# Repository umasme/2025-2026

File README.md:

# 🚀 NASA Lunabotics 2026 — University of Miami ASME

Robust, ROS 2–based software stack and supporting assets for our lunar excavation rover.  
This repository houses **software, hardware, simulation, datasets, and documentation** to support the NASA Lunabotics 2026 competition.  

---
## To Build
1. Download Docker
2. Open VS Code and switch to WS directory
3. Install the dev containers extension
4. Control + Shift + P to access command palette
5. Search for Dev Containers: Reopen in Container
6. Voila

## Sensors
1. D435i (TBD)
2. Oak D-lite (TBD)
3. Power sensor
4. Encoders
5. Linear encoders
6. Cameras

## Actuators
1. Four motors
2. Linear Actuators

## After Each Commit
Update DEVLOG.md with a summary of changes. Commits shall be made to the develop branch after main branch docker is working.

## 📖 Project Overview

Our rover integrates:

- **Perception** — stereo depth, object detection, terrain mapping  
- **Localization & Navigation** — SLAM, sensor fusion, path planning  
- **Autonomy** — state machines / behavior trees for excavation & hauling  
- **Control & Teleop** — motor drivers, teleop interfaces, web dashboard  
- **Simulation** — Ignition Gazebo worlds, scenarios, and URDF models  
- **Documentation** — aligned with NASA Systems Engineering (SRR, PDR, CDR, ConOps)  

---

## 📂 Repository Layout

```text
lunabotics-2025/
├─ README.md                     # Project overview (this file)
├─ LICENSE
├─ .github/workflows/            # CI/CD pipelines
├─ .devcontainer/                # VS Code Dev Containers
├─ docker/                       # Development & runtime Dockerfiles
├─ docs/                         # Documentation
│  ├─ index.md
│  ├─ ConOps/                    # SRR/PDR/CDR deliverables
│  ├─ Architectures/             # Block/state diagrams
│  ├─ MissionRules/              # Ops rules, FMEA links
│  ├─ Tutorials/                 # Step-by-step guides
│  └─ Calibration/               # Sensor/actuator calibration
├─ hardware/                     # Mechanical + electrical
│  ├─ electrical/                # Schematics, PCB, BOM
│  ├─ mechanical/                # CAD models, drawings
│  └─ configs/                   # Wiring tables, pin maps
├─ datasets/                     # Large files (via Git LFS)
│  ├─ bags/                      # ROS bag recordings
│  ├─ maps/                      # Occupancy/elevation maps
│  └─ test_scenes/               # Images, point clouds
├─ sim/                          # Simulation assets
│  ├─ worlds/                    # Ignition/Gazebo worlds
│  ├─ models/                    # URDF meshes, STL/DAE
│  └─ scenarios/                 # Scenario configs
├─ examples/                     # Cross-package & full-system demos
│  ├─ sim_demo.launch.py
│  ├─ teleop_example.md
│  └─ rviz_configs/
├─ tools/                        # Utility scripts
│  ├─ log_tools/                 # Bag→CSV, plotting
│  ├─ calibration/               # Camera/IMU calibration
│  ├─ deploy/                    # Deployment helpers
│  └─ ci/                        # CI support scripts
└─ ros2_ws/                      # ROS 2 workspace
   ├─ src/
   │  ├─ lunabotics_bringup/     # System launch & params
   │  ├─ lunabotics_description/ # URDF/Xacro and meshes
   │  ├─ lunabotics_msgs/        # Custom messages & services
   │  ├─ lunabotics_hw/          # Hardware drivers
   │  ├─ lunabotics_perception/  # Cameras, detection
   │  ├─ lunabotics_mapping/     # SLAM & maps
   │  ├─ lunabotics_localization/# State estimation
   │  ├─ lunabotics_navigation/  # Planning & control
   │  ├─ lunabotics_control/     # Low-level control loops
   │  ├─ lunabotics_mission/     # Autonomy FSM/BT
   │  ├─ lunabotics_teleop/      # Joystick / keyboard teleop
   │  ├─ lunabotics_dashboard/   # Web UI & ROS bridge
   │  └─ lunabotics_sim/         # Simulation plugins & launches
   ├─ build/                     # (ignored) colcon build output
   ├─ install/                   # (ignored) colcon install
   └─ log/                       # (ignored) colcon logs

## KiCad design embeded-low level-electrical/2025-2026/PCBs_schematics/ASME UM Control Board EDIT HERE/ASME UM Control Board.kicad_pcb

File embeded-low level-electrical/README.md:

# 🚀 ASME Lunabotics 2026 University of Miami – Electrical Subsystem

Welcome to the official repository for the electrical subsystem of the University of Miami’s ASME Lunabotics team for the **2026 NASA Lunabotics Competition**.

---

This repository documents the design, implementation, and testing of the rover’s electrical system, emphasizing high reliability, efficiency, and simplicity.

# 2026 Design Goals

- Design an effective system with high reliability, minimal points of failure, and strategic redundancies while keeping it simple with minimal components and maximum efficiency.

- Focus on real-time data logging of current, voltage, power, temperature, and speed for post-analysis and future optimization.

- Reduce wiring complexity by using multiplexed communication protocols.

- Ensure reliable wired communication and power distribution to motors and other subsystems.
---
# 2026 Proposed Electrical Architecture

<p align="center">
  
  <p align="center">
  <b> High Voltage Electrical Architecture </b>
  </p>
</p>

  <p align="center">
  <b> Control Electrical Architecture </b>
  </p>

---
## High-Current Power Distribution Board
This high-current board distributes power to all outputs, including the four drivetrain motors, the excavation motor, the deposition motor, and two linear actuators.

<p align="center">
  <b> High-Current Power Distribution Board PCB </b>
</p>

For more details refer to this link: [to be added]

---
## Low-Level Control Board based on Teensy 4.1

<p align="center">
  <b> Low-Level Control Board based on Teensy 4.1 PCB </b>
</p>

For more details refer to this link: [To be added]

---
##  🎯2026 Season Plan 
We finalized the season plan for 2026 for the electrical subsystem with detailed performance analysis for each part we used in the electrical system and proposed improvement.

**[Click here to access the 2025 season plan](https://www.overleaf.com/read/gmnmmjygcdmp#dd8f39)**

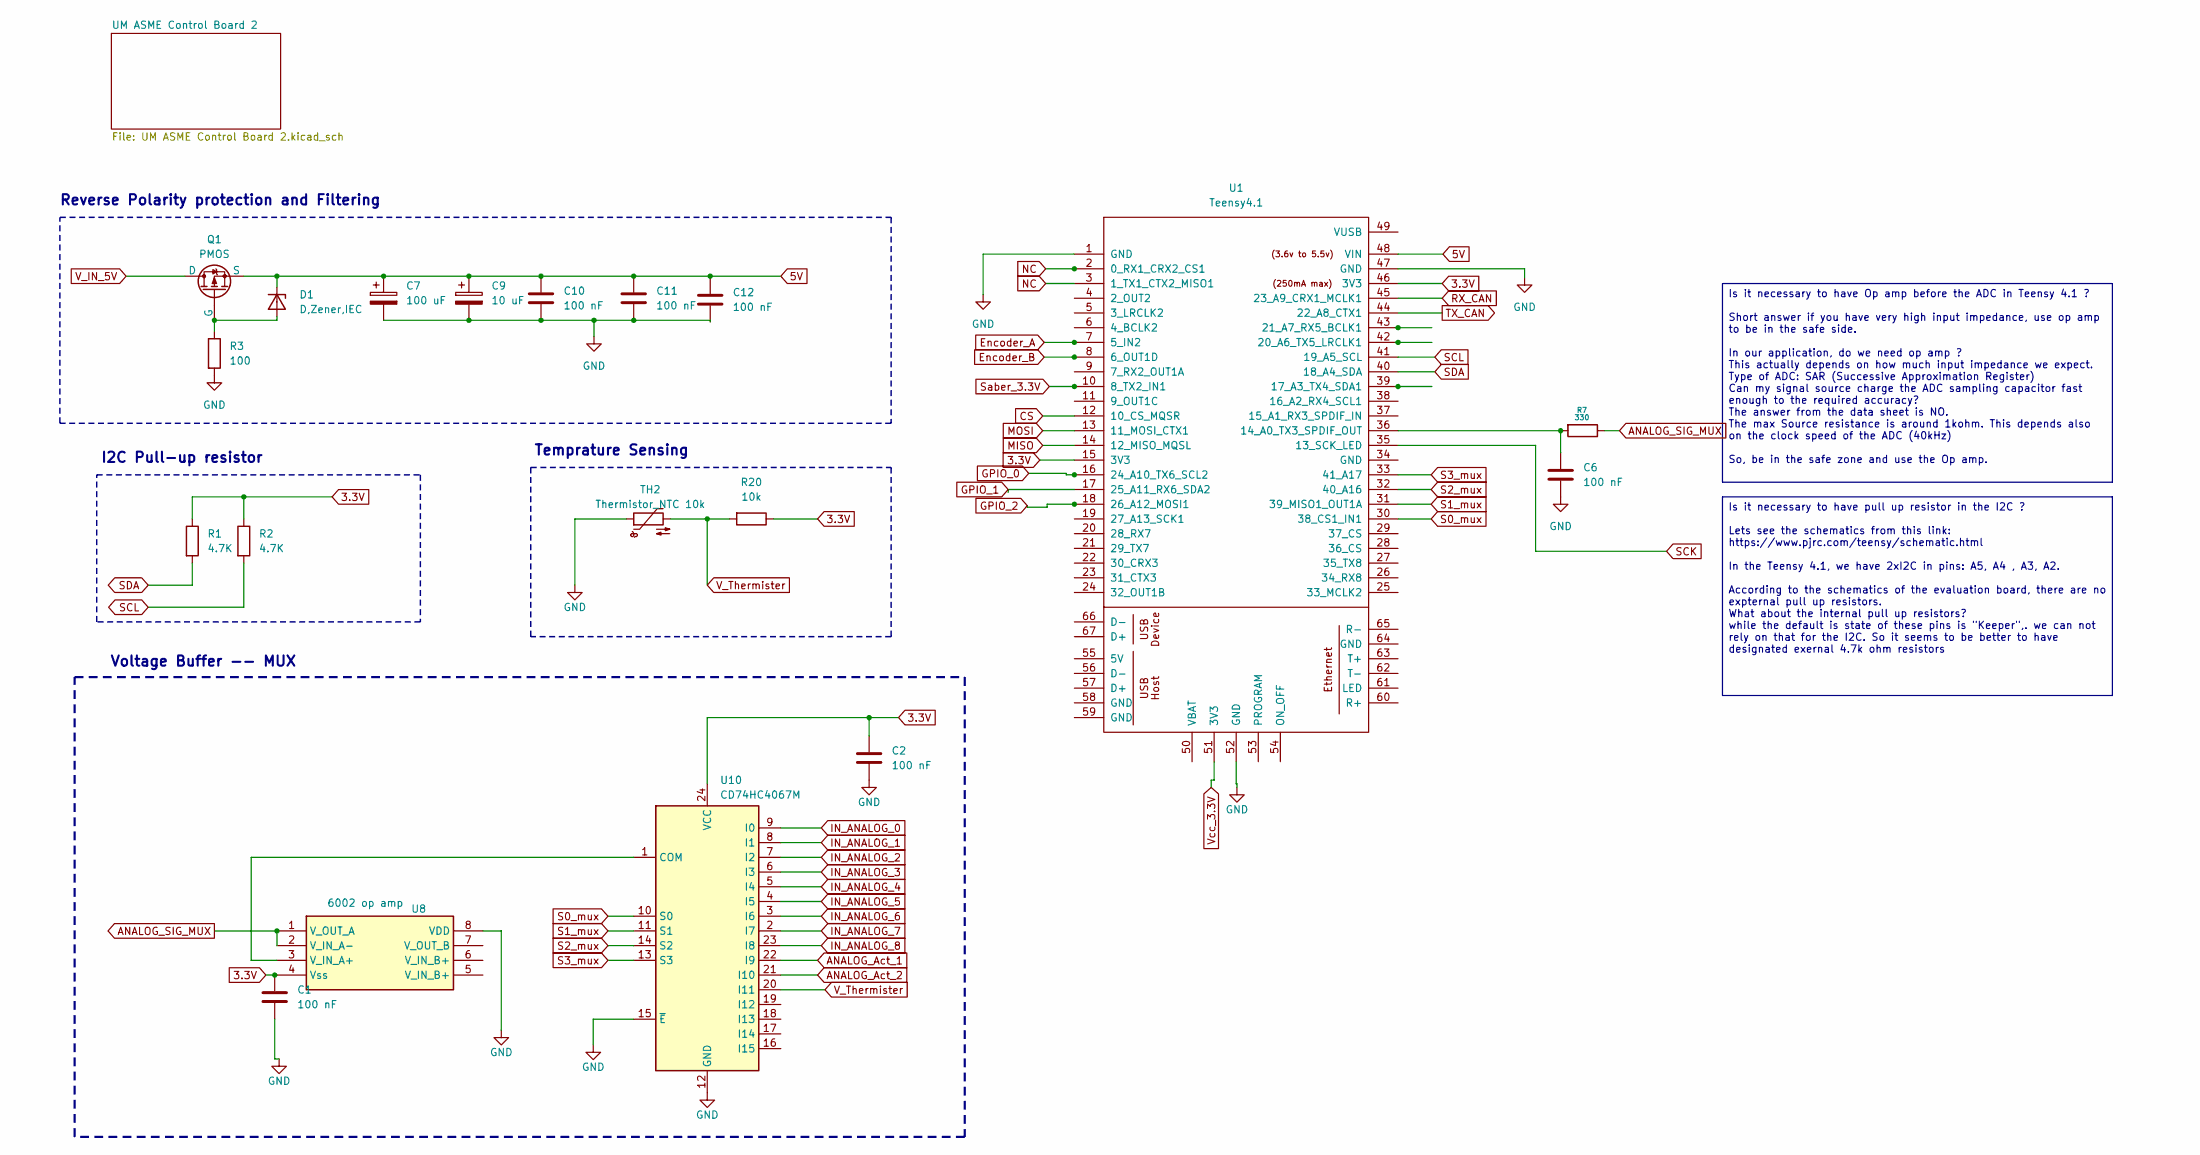
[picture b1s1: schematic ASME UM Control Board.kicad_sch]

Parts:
C1, C2, C6, C10, C11, C12: 100 nF; C_1206_3216Metric_Pad1.33x1.80mm_HandSolder
C7: 100 uF; CP_Radial_D8.0mm_P2.50mm
C9: 10 uF; C_1206_3216Metric_Pad1.33x1.80mm_HandSolder
D1: D,Zener,IEC; D_DO-35_SOD27_P7.62mm_Horizontal
Q1: PMOS; TO-220-3_Vertical
R1, R2: 4.7K; R_1206_3216Metric_Pad1.30x1.75mm_HandSolder
R3: 100; R_1206_3216Metric_Pad1.30x1.75mm_HandSolder
R7: 330; R_1206_3216Metric_Pad1.30x1.75mm_HandSolder
R20: 10k; R_1206_3216Metric_Pad1.30x1.75mm_HandSolder
TH2: Thermistor_NTC 10k; 1210
U1: Teensy4.1; Teensy41
U8: 6002 op amp; DIP-8_W7.62mm_LongPads
U10: CD74HC4067M; SOIC-24W_7.5x15.4mm_P1.27mm

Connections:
3.3V: C1.1, C2.1, R1.1, R2.1, R20.1, U1.15 (3V3), U1.46 (3V3), U8.4 (Vss), U10.24 (VCC); also elsewhere on the board
5V: C7.1, C9.1, C10.1, C11.1, C12.1, D1.1 (K-), Q1.3 (S), U1.48 (VIN); also elsewhere on the board
ANALOG_Act_1: U10.22 (I9); also elsewhere on the board
ANALOG_Act_2: U10.21 (I10); also elsewhere on the board
ANALOG_SIG_MUX: R7.1, U8.1 (V_OUT_A), U8.2 (V_IN_A-)
CS: U1.12 (10_CS_MQSR)
Encoder_A: U1.7 (5_IN2); also elsewhere on the board
Encoder_B: U1.8 (6_OUT1D); also elsewhere on the board
GND: C1.2, C2.2, C6.2, C7.2, C9.2, C10.2, C11.2, C12.2, R3.2, TH2.1, U1.1 (GND), U1.47 (GND), U1.52 (GND), U8.8 (VDD), U10.12 (GND), U10.15 (~E); also elsewhere on the board
GPIO_0: U1.16 (24_A10_TX6_SCL2); also elsewhere on the board
GPIO_1: U1.17 (25_A11_RX6_SDA2); also elsewhere on the board
GPIO_2: U1.18 (26_A12_MOSI1); also elsewhere on the board
IN_ANALOG_0: U10.9 (I0); also elsewhere on the board
IN_ANALOG_1: U10.8 (I1); also elsewhere on the board
IN_ANALOG_2: U10.7 (I2); also elsewhere on the board
IN_ANALOG_3: U10.6 (I3); also elsewhere on the board
IN_ANALOG_4: U10.5 (I4); also elsewhere on the board
IN_ANALOG_5: U10.4 (I5); also elsewhere on the board
IN_ANALOG_6: U10.3 (I6); also elsewhere on the board
IN_ANALOG_7: U10.2 (I7); also elsewhere on the board
IN_ANALOG_8: U10.23 (I8); also elsewhere on the board
MISO: U1.14 (12_MISO_MQSL)
MOSI: U1.13 (11_MOSI_CTX1)
NC: U1.2 (0_RX1_CRX2_CS1), U1.3 (1_TX1_CTX2_MISO1)
unnamed: D1.2 (A+), Q1.2 (G), R3.1
unnamed: C6.1, R7.2, U1.36 (14_A0_TX3_SPDIF_OUT)
unnamed: U8.3 (V_IN_A+), U10.1 (COM)
RX_CAN: U1.45 (23_A9_CRX1_MCLK1); also elsewhere on the board
S0_mux: U1.30 (38_CS1_IN1), U10.10 (S0)
S1_mux: U1.31 (39_MISO1_OUT1A), U10.11 (S1)
S2_mux: U1.32 (40_A16), U10.14 (S2)
S3_mux: U1.33 (41_A17), U10.13 (S3)
SCK: U1.35 (13_SCK_LED)
SCL: R2.2, U1.41 (19_A5_SCL); also elsewhere on the board
SDA: R1.2, U1.40 (18_A4_SDA); also elsewhere on the board
Saber_3.3V: U1.10 (8_TX2_IN1); also elsewhere on the board
TX_CAN: U1.44 (22_A8_CTX1); also elsewhere on the board
V_IN_5V: Q1.1 (D); also elsewhere on the board
V_Thermister: R20.2, TH2.2, U10.20 (I11)

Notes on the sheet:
Voltage Buffer -- MUX
Temprature Sensing
Reverse Polarity protection and Filtering
I2C Pull-up resistor
Is it necessary to have Op amp before the ADC in Teensy 4.1 ? Short answer if you have very high input impedance, use op amp to be in the safe side. In our application, do we need op amp ? This actually depends on how much input impedance we expect. Type of ADC: SAR (Successive Approximation Regist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
Is it necessary to have pull up resistor in the I2C ? Lets see the schematics from this link: https://www.pjrc.com/teensy/schematic.html In the Teensy 4.1, we have 2xI2C in pins: A5, A4 , A3, A2. According to the schematics of the evaluation board, there are no expternal pull up resistors. What abo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

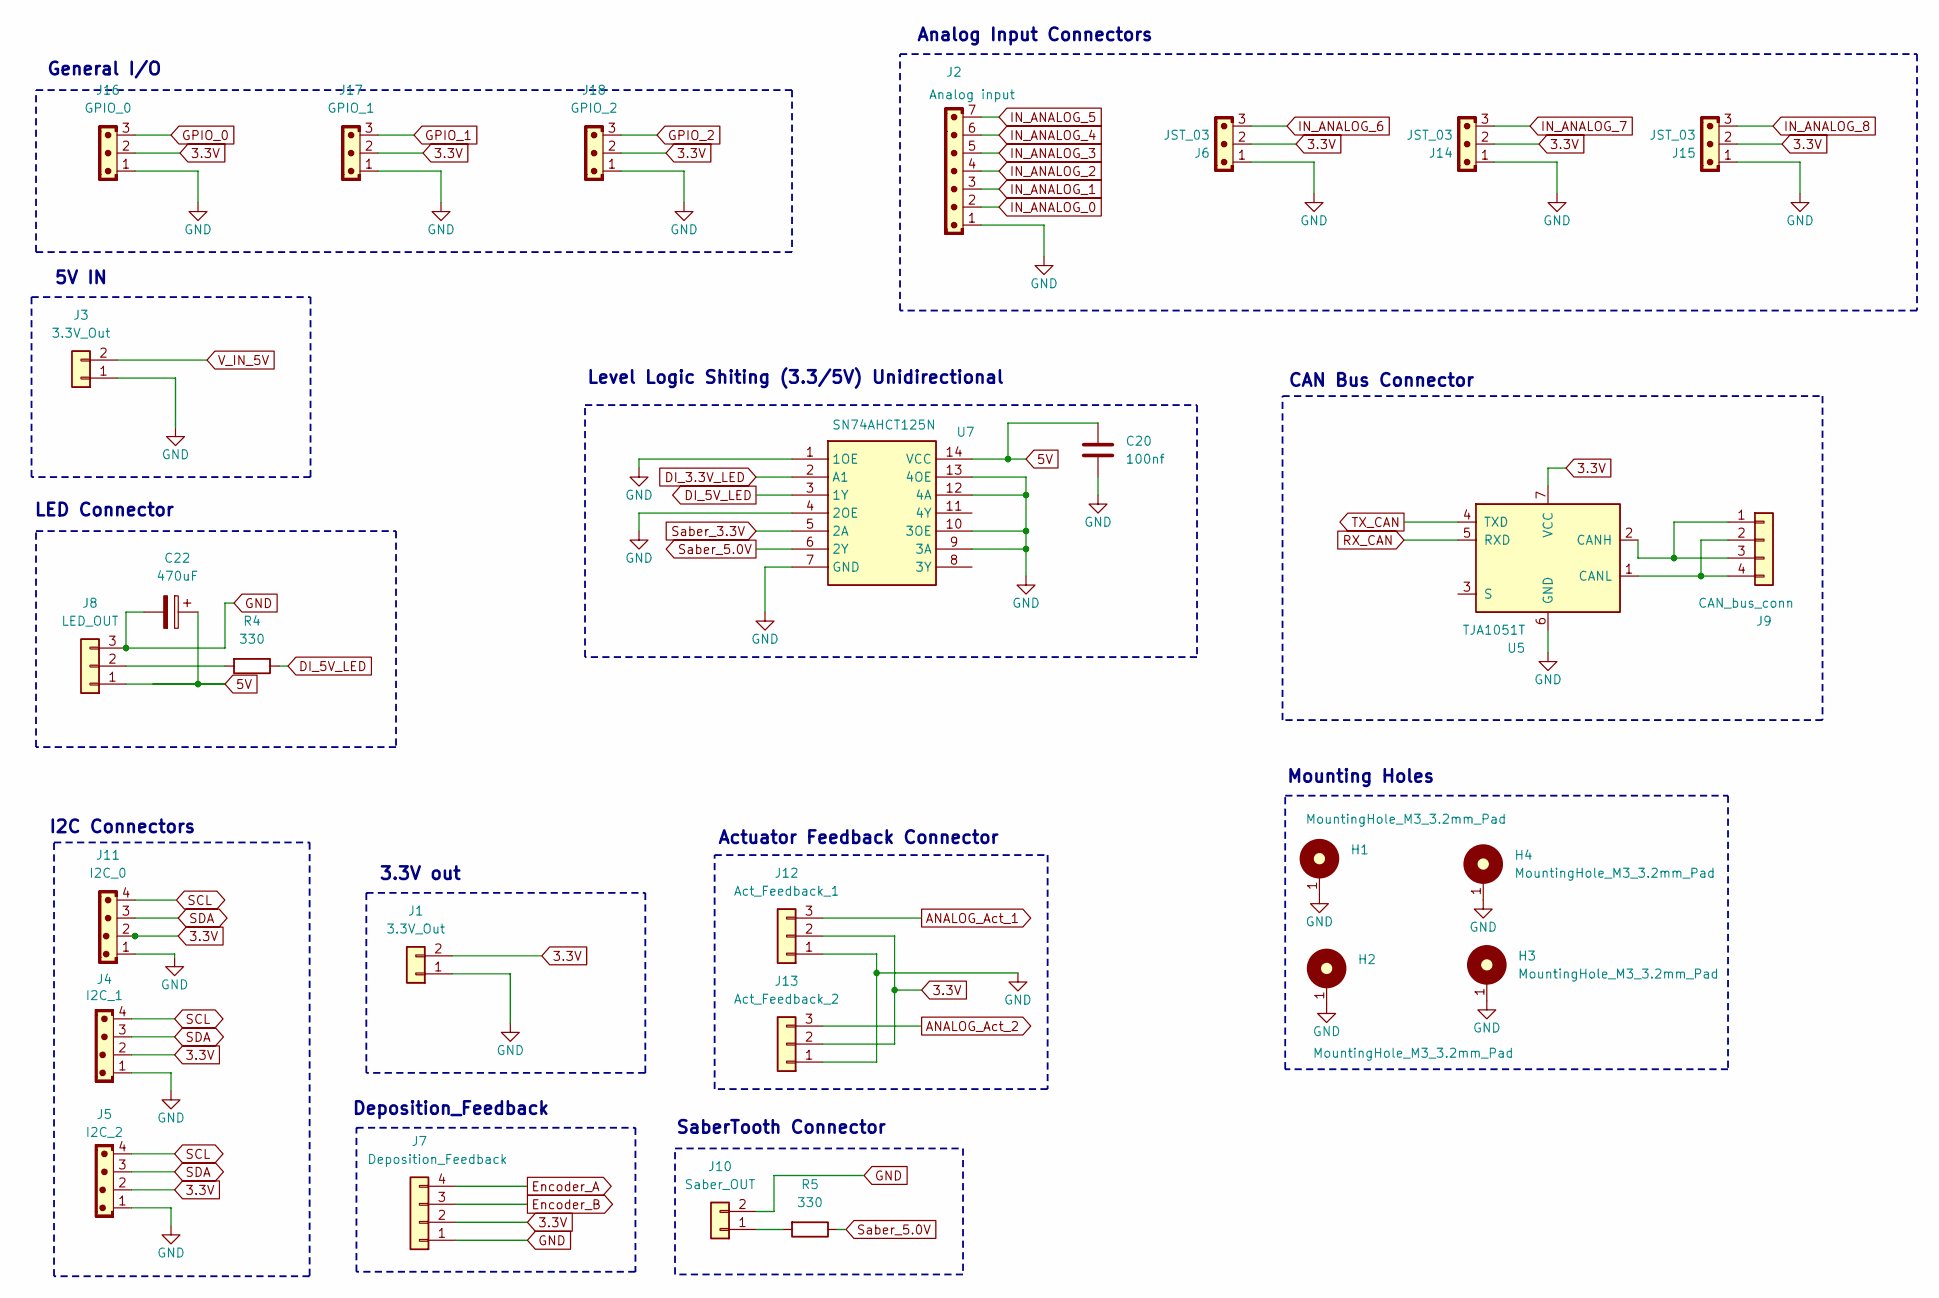
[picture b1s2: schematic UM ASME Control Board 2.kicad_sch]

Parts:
C20: 100nf; C_1206_3216Metric_Pad1.33x1.80mm_HandSolder
C22: 470uF; CP_Radial_D10.0mm_P3.80mm
H1, H2, H3, H4: MountingHole_M3_3.2mm_Pad; MountingHole_3.2mm_Pad
J1: 3.3V_Out; JST_PH_B2B-PH-K_1x02_P2.00mm_Vertical
J2: Analog input; JST_PH_B7B-PH-K_1x07_P2.00mm_Vertical
J3: 3.3V_Out; AMASS_XT30UPB-M_1x02_P5.0mm_Vertical
J4: I2C_1; JST_PH_B4B-PH-K_1x04_P2.00mm_Vertical
J5: I2C_2; JST_PH_B4B-PH-K_1x04_P2.00mm_Vertical
J6, J14, J15: JST_03; JST_PH_B3B-PH-K_1x03_P2.00mm_Vertical
J7: Deposition_Feedback; JST_PH_B4B-PH-K_1x04_P2.00mm_Vertical
J8: LED_OUT; JST_EH_B3B-EH-A_1x03_P2.50mm_Vertical
J9: CAN_bus_conn; JST_PH_B4B-PH-K_1x04_P2.00mm_Vertical
J10: Saber_OUT; JST_PH_B2B-PH-K_1x02_P2.00mm_Vertical
J11: I2C_0; JST_PH_B4B-PH-K_1x04_P2.00mm_Vertical
J12: Act_Feedback_1; JST_PH_B3B-PH-K_1x03_P2.00mm_Vertical
J13: Act_Feedback_2; JST_PH_B3B-PH-K_1x03_P2.00mm_Vertical
J16: GPIO_0; JST_PH_B3B-PH-K_1x03_P2.00mm_Vertical
J17: GPIO_1; JST_PH_B3B-PH-K_1x03_P2.00mm_Vertical
J18: GPIO_2; JST_PH_B3B-PH-K_1x03_P2.00mm_Vertical
R4, R5: 330; R_1206_3216Metric_Pad1.30x1.75mm_HandSolder
U5: TJA1051T; PinHeader_1x07_P2.54mm_Vertical
U7: SN74AHCT125N; DIP-14_W7.62mm_LongPads

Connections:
3.3V: J1.2, J4.2, J5.2, J6.2, J7.2, J11.2, J12.2, J13.2, J14.2, J15.2, J16.2, J17.2, J18.2, U5.7 (VCC); also elsewhere on the board
5V: C20.2, C22.1, J8.1, U7.14 (VCC); also elsewhere on the board
ANALOG_Act_1: J12.3; also elsewhere on the board
ANALOG_Act_2: J13.3; also elsewhere on the board
DI_3.3V_LED: U7.2 (A1)
DI_5V_LED: R4.1, U7.3 (1Y)
Encoder_A: J7.4; also elsewhere on the board
Encoder_B: J7.3; also elsewhere on the board
GND: C20.1, C22.2, H1.1, H2.1, H3.1, H4.1, J1.1, J2.1, J3.1, J4.1, J5.1, J6.1, J7.1, J8.3, J10.2, J11.1, J12.1, J13.1, J14.1, J15.1, J16.1, J17.1, J18.1, U5.6 (GND), U7.1 (1OE), U7.4 (2OE), U7.7 (GND), U7.9 (3A), U7.10 (3OE), U7.12 (4A), U7.13 (4OE); also elsewhere on the board
GPIO_0: J16.3; also elsewhere on the board
GPIO_1: J17.3; also elsewhere on the board
GPIO_2: J18.3; also elsewhere on the board
IN_ANALOG_0: J2.2; also elsewhere on the board
IN_ANALOG_1: J2.3; also elsewhere on the board
IN_ANALOG_2: J2.4; also elsewhere on the board
IN_ANALOG_3: J2.5; also elsewhere on the board
IN_ANALOG_4: J2.6; also elsewhere on the board
IN_ANALOG_5: J2.7; also elsewhere on the board
IN_ANALOG_6: J6.3; also elsewhere on the board
IN_ANALOG_7: J14.3; also elsewhere on the board
IN_ANALOG_8: J15.3; also elsewhere on the board
unnamed: J8.2, R4.2
unnamed: J9.1, J9.3, U5.2 (CANH)
unnamed: J9.2, J9.4, U5.1 (CANL)
unnamed: J10.1, R5.2
RX_CAN: U5.5 (RXD); also elsewhere on the board
SCL: J4.4, J5.4, J11.4; also elsewhere on the board
SDA: J4.3, J5.3, J11.3; also elsewhere on the board
Saber_3.3V: U7.5 (2A); also elsewhere on the board
Saber_5.0V: R5.1, U7.6 (2Y)
TX_CAN: U5.4 (TXD); also elsewhere on the board
V_IN_5V: J3.2; also elsewhere on the board

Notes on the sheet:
3.3V out
I2C Connectors
Deposition_Feedback
Level Logic Shiting (3.3/5V) Unidirectional
Mounting Holes
LED Connector
General I/O
5V IN
Actuator Feedback Connector
CAN Bus Connector
Analog Input Connectors
SaberTooth Connector

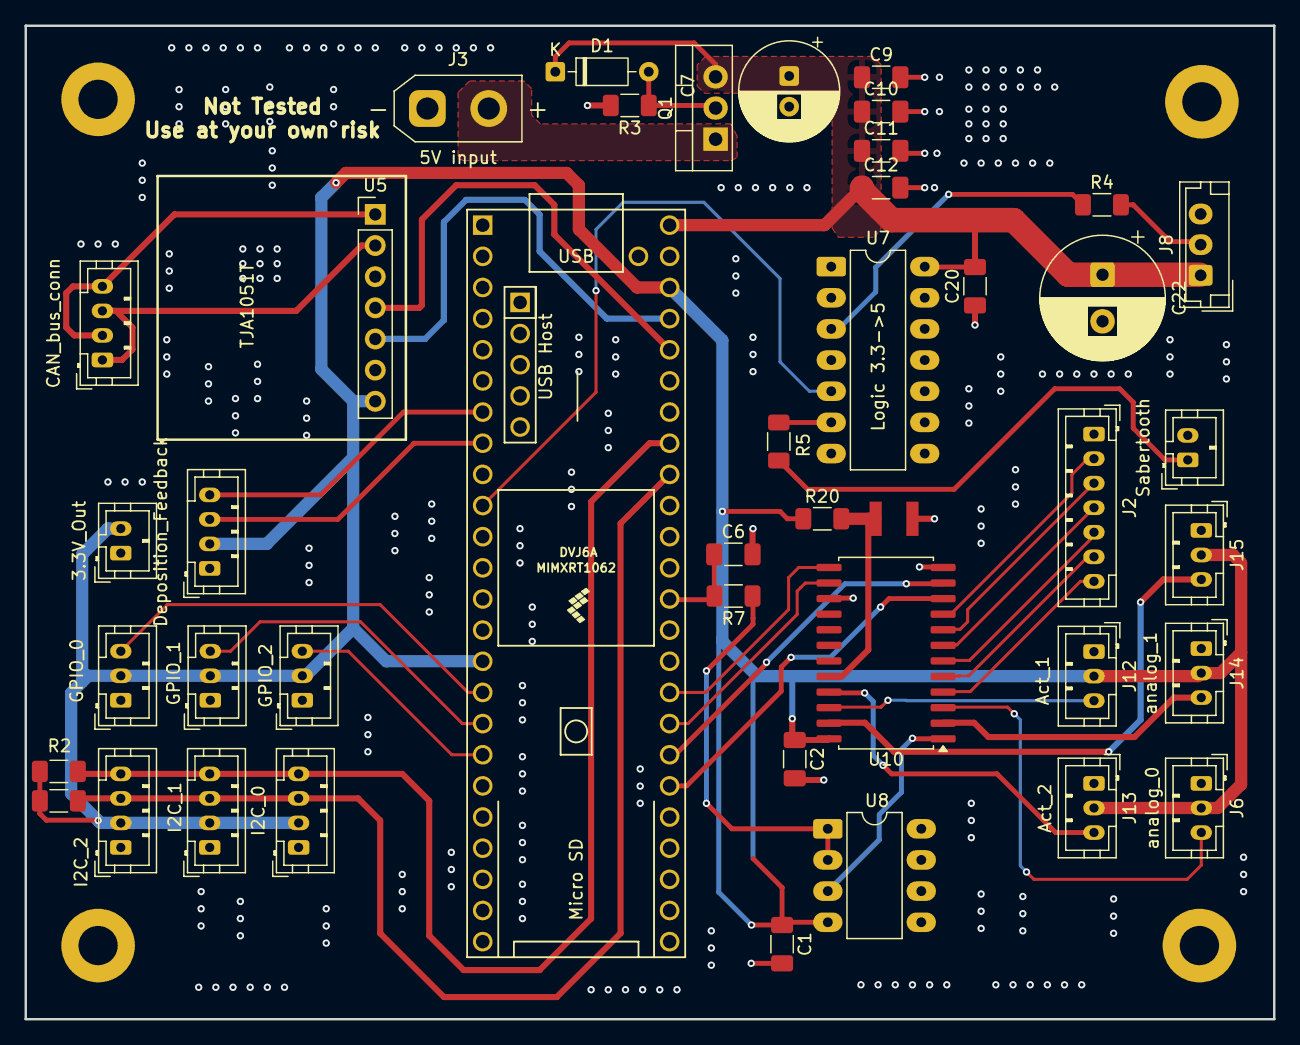
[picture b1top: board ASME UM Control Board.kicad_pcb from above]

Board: 4 copper layers, 101.8 x 81.0 mm, 47 parts (0 on the bottom side), 41 nets.

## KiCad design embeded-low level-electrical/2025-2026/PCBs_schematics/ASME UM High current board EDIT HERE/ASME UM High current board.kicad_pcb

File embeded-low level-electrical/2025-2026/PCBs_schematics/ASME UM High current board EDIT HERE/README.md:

# High-Current Power Distribution Board (PDB)

## Overview
The High-Current Power Distribution Board (PDB) is designed to safely and efficiently distribute electrical power to all high-power subsystems of the rover. It serves as the central power hub, handling high transient currents while providing protection, diagnostics, and future expandability.

## Supported Loads
This board distributes power to the following subsystems:

* **4×** Drivetrain motors (BLDC)
* **1×** Excavation motor (BLDC)
* **1×** Deposition motor (DC)
* **2×** Linear actuators 

> **Note:** The Jetson Nano is powered through an external power supply with a dedicated DC-DC converter and is **not** powered directly from this board.

## Electrical Capabilities
* **Peak Current:** Supports up to **40 A** peak current during startup and transient conditions.
* **Output Configuration:**
  * Minimum of **7** high-current outputs.
  * **1** dedicated output for a DC-DC converter.

## Board Features
* **Protection:** Reverse-polarity protection on the main power input and individual fuses for each output bus. (To be added)
* **Diagnostics:**
  * Power indication LED for board power status.
  * Individual LED indicators for each output to identify blown or faulted fuses.
* **Stability:** Decoupling capacitors for voltage stability and noise reduction.
* **Mechanical:** Defined mounting holes for secure mechanical integration.
* **Current Sensing:**
  * Initial revision includes main bus current sensor (or limited sensors).
  * PCB design preserves expandability for future per-output current sensing.
* ** Add-ons:**
  * Onboard DC-DC buck converter based on AP64502Q synchronous DC-DC buck converter (5V/5A). 
  * Linear 3.3 V regulator (not required for current system architecture).

## PCB Design Considerations
* **High-Current Optimization:** Adhered to IPC-2221 standards for power plane optimization to handle high-current loads and manage thermal dissipation.
* **Component Layout:** Strictly followed the recommended layout guidelines specified in the [AP64502Q DC-DC Converter Datasheet](https://www.diodes.com/datasheet/download/AP64502Q.pdf) to minimize noise and ensure stability.
* **Power Integrity Analysis:** Utilized Altium's Power Analyzer tool to simulate current density and eliminate bottlenecks.
<h3>Power Analyzer Results</h3>
<table width="100%">
  <tr>
    <th width="50%">Before Optimization</th>
    <th width="50%">After Optimization</th>
  </tr>
  <tr>
    <td align="center">
      
    </td>
    <td align="center">
      
    </td>
  </tr>
</table>## Design Objectives
* **Reliability:** Consistent operation under high-current and transient conditions.
* **Efficiency:** Low-resistance power paths to minimize voltage drop.
* **Usability:** Clear visual diagnostics for fast fault identification.

## Safety and Protection
* **Input:** Reverse-polarity protection.
* **Output:** Fuse protection per channel.
* **Visuals:** Fault detection via LED indicators.
* **Noise:** Electrical noise suppression using decoupling capacitors.

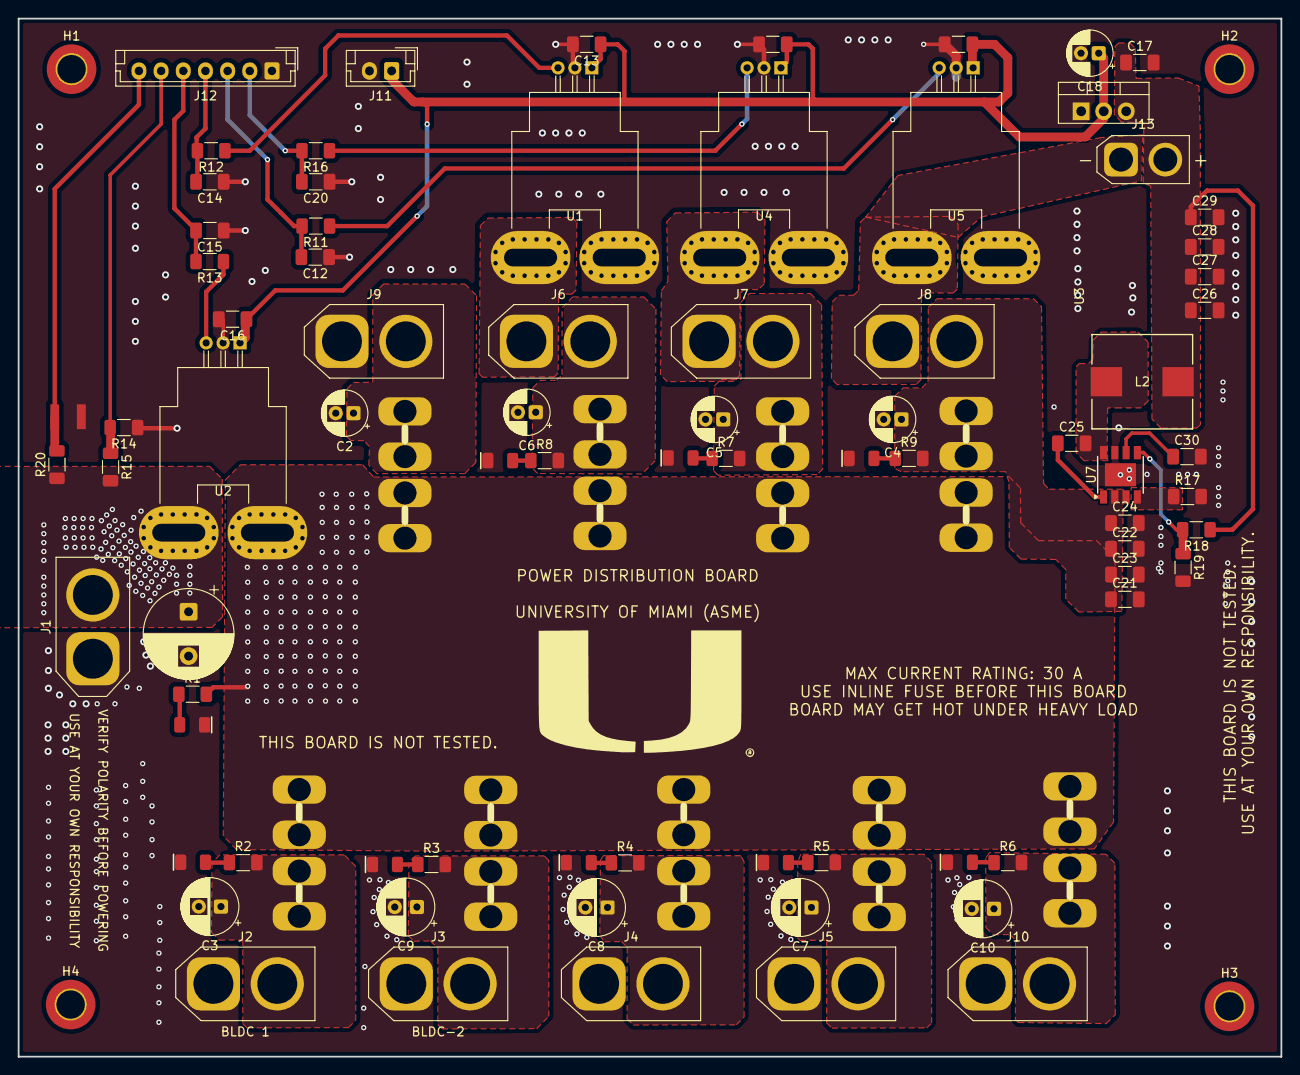
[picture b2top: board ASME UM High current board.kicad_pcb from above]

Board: 2 copper layers, 142.4 x 117.1 mm, 92 parts (0 on the bottom side), 41 nets.

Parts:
C1: 1000uF_16V; CP_Radial_D10.0mm_P5.00mm
C2, C4, C5, C6: 10uF_16V; CP_Radial_D5.0mm_P2.00mm
C3, C7, C8, C9, C10: 100uF_25V; CP_Radial_D6.3mm_P2.50mm
C11, C13, C16, C19: 100nF_Ceramic; C_1206_3216Metric_Pad1.33x1.80mm_HandSolder
C12, C14, C15, C20: 100nF; C_1206_3216Metric_Pad1.33x1.80mm_HandSolder
C17, C25, C26: 0.1uF; C_1206_3216Metric_Pad1.33x1.80mm_HandSolder
C18: 10uF; CP_Radial_D5.0mm_P2.00mm
C21: Open; C_1206_3216Metric_Pad1.33x1.80mm_HandSolder
C22, C23, C24: 10uF; C_1206_3216Metric_Pad1.33x1.80mm_HandSolder
C27, C28, C29: 47uF; C_1206_3216Metric_Pad1.33x1.80mm_HandSolder
C30: 10nF; C_1206_3216Metric_Pad1.33x1.80mm_HandSolder
D1: Red; LED_1206_3216Metric_Red
D2, D3, D4, D5, D6, D7, D8, D9: Green; LED_1206_3216Metric_Green
F1, F2, F3, F4, F5, F6, F7, F8, F9: Blade Fuse; Fuseholder_Automotive
H1, H2, H3, H4: MountingHole_M3; MountingHole_3.2mm_M3_DIN965_Pad_TopBottom
J1: From main battery; AMASS_XT60-M_1x02_P7.20mm_Vertical
J2: BLDC 1; AMASS_XT60-M_1x02_P7.20mm_Vertical
J3: BLDC-2; AMASS_XT60-M_1x02_P7.20mm_Vertical
J4: BLDC-3; AMASS_XT60-M_1x02_P7.20mm_Vertical
J5: BLDC-4; AMASS_XT60-M_1x02_P7.20mm_Vertical
J6: Actuators; AMASS_XT60-M_1x02_P7.20mm_Vertical
J7: Deposition; AMASS_XT60-M_1x02_P7.20mm_Vertical
J8: 5V DC-DC; AMASS_XT60-M_1x02_P7.20mm_Vertical
J9: Extra; AMASS_XT60-M_1x02_P7.20mm_Vertical
J10: BLDC-5; AMASS_XT60-M_1x02_P7.20mm_Vertical
J11: 3.3V_IN; JST_EH_B2B-EH-A_1x02_P2.50mm_Vertical
J12: JST_07; JST_EH_B7B-EH-A_1x07_P2.50mm_Vertical
J13: 5V_OUT; AMASS_XT30U-M_1x02_P5.0mm_Vertical
L2: 6.8uH; IND_PCC-M1040LP_PAN-M
R1: 1.5k; R_1206_3216Metric_Pad1.30x1.75mm_HandSolder
R2, R3, R4, R5, R6, R7, R8, R9: 1.2k; R_1206_3216Metric_Pad1.30x1.75mm_HandSolder
R11, R12, R13, R16: 4.7k; R_1206_3216Metric_Pad1.30x1.75mm_HandSolder
R14: 20k; R_1206_3216Metric_Pad1.30x1.75mm_HandSolder
R15: 100k; R_1206_3216Metric_Pad1.30x1.75mm_HandSolder
R17: 200k; R_1206_3216Metric_Pad1.30x1.75mm_HandSolder
R18: 52.3k; R_1206_3216Metric_Pad1.30x1.75mm_HandSolder
R19: 10k; R_1206_3216Metric_Pad1.30x1.75mm_HandSolder
R20: 47k; R_1206_3216Metric_Pad1.30x1.75mm_HandSolder
TH1: Thermistor_NTC 10k; 1210
U1, U4, U5: ACS758xCB-050B-PFF; Allegro_CB_PFF
U2: ACS772xCB-050B-PFF; Allegro_CB_PFF
U3: LD1117V33; TO-220-3_Vertical
U7: AP64502QSP‑13; Diodes_SO-8EP

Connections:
3.3V: C11.1, C13.1, C16.1, C18.1, C19.1, J11.1, U1.1 (VCC), U2.1 (VCC), U3.2 (VO), U4.1 (VCC), U5.1 (VCC)
5V_out: C17.1, C26.1, C27.1, C28.1, C29.1, J13.2, L2.2, R18.1, U3.3 (VI)
14V: C1.1, J1.2, R15.2, R20.1, U2.4 (IP+)
I_In_1: J6.1, U1.4 (IP+)
I_In_2: J7.1, U4.4 (IP+)
I_In_4: J8.1, J13.1, U5.4 (IP+)
I_Out_1: C1.2, C2.2, C3.2, C4.2, C5.2, C6.2, C7.2, C8.2, C9.2, C10.2, C11.2, C12.1, C13.2, C14.1, C15.1, C16.2, C17.2, C18.2, C19.2, C20.1, C21.2, C22.2, C23.2, C24.2, C26.2, C27.2, C28.2, C29.2, C30.2, D1.1 (K), D2.1 (K), D3.1 (K), D4.1 (K), D5.1 (K), D6.1 (K), D7.1 (K), D8.1 (K), D9.1 (K), J1.1, J2.1, J3.1, J4.1, J5.1, J9.1, J10.1, J11.2, J12.1, R14.1, R17.2, R19.2, TH1.1, U1.2 (GND), U1.5 (IP-), U2.2 (GND), U3.1 (GND), U4.2 (GND), U4.5 (IP-), U5.2 (GND), U5.5 (IP-), U7.7 (GND), U7.9 (GND)
I_Out_3: F1.2, F2.2, F3.2, F4.2, F5.2, F6.2, F7.2, F8.2, F9.2, R1.2, U2.5 (IP-)
unnamed: C2.1, F9.1, J9.2
unnamed: C3.1, F1.1, J2.2, R2.2
unnamed: C5.1, F7.1, J7.2, R7.2
unnamed: C6.1, F6.1, J6.2, R8.2
unnamed: C7.1, F4.1, J5.2, R5.2
unnamed: C8.1, F3.1, J4.2, R4.2
unnamed: C9.1, F2.1, J3.2, R3.2
unnamed: C10.1, F5.1, J10.2, R6.2
unnamed: D1.2 (A), R1.1
unnamed: D2.2 (A), R2.1
unnamed: D3.2 (A), R3.1
unnamed: D4.2 (A), R4.1
unnamed: D5.2 (A), R5.1
unnamed: D6.2 (A), R6.1
unnamed: D7.2 (A), R8.1
unnamed: D8.2 (A), R7.1
unnamed: D9.2 (A), R9.1
unnamed: R12.1, U1.3 (VIOUT)
unnamed: R13.1, U2.3 (VIOUT)
unnamed: R16.1, U4.3 (VIOUT)
unnamed: R11.1, U5.3 (VIOUT)
unnamed: C25.1, U7.1 (BST)
unnamed: R18.2, R19.1, U7.5 (FB)
unnamed: R17.1, U7.4 (RT/CLK)
unnamed: C30.1, U7.6 (SS)
unnamed: C25.2, L2.1, U7.8 (SW)
V_ANALOG_0: J12.6, R14.2, R15.1
V_ANALOG_1: C14.2, J12.4, R12.2
V_ANALOG_2: C20.2, J12.2, R16.2
V_ANALOG_3: C15.2, J12.5, R13.2
V_ANALOG_4: C12.2, J12.3, R11.2
V_ANALOG_5: J12.7, R20.2, TH1.2
V_in_DC-DC: C4.1, C21.1, C22.1, C23.1, C24.1, F8.1, J8.2, R9.2, U7.2 (Vin), U7.3 (EN)

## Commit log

2025-08-29 docs: Create Architecture.md
2025-08-29 docs: Add contributing guidelines to CONTRIBUTING.md
2025-08-29 feat: create ci.yaml
2025-08-29 docs: Create Makefile.md for command documentation
    Add a section for commonly used commands.
2025-08-29 docs: Add section for software architecture details
2025-08-29 Add initial README for Docker usage
2025-08-29 docs: Add README for electrical schematics
2025-08-29 docs: Add initial README for ROS project
2025-08-29 feat: Delete .github/workflows/ci.yaml
    This is good to have but is spamming my email
2025-08-29 docs: Add initial README for tools directory
2025-08-29 docs: Add README for Gazebo worlds
2025-08-29 docs: Add README for meshes in models directory
2025-08-29 docs: Revise README for NASA Lunabotics 2025 project
    Updated project description and repository layout.
2025-09-03 feat: Add devcontainer setup for ROS 2 workspace
    Introduces Dockerfile and devcontainer.json for VS Code development environment in ws/.devcontainer, targeting ROS 2. Also renames ros2_ws/README.md to ws/README.md for consistency.
2025-09-03 docs: Update README with build and commit instructions
2025-09-03 docs: Document devcontainer setup changes in DEVLOG.md
2025-09-05 docs: Add sensors and actuators sections to README
    Added sections for sensors and actuators in README.
2025-09-09 Added test package.
2025-09-09 Created new Dockerfile.
2025-09-09 Changed dev container folder location.
2025-09-09 Changed dockerfile location.
2025-09-09 Fixed issue in Dockerfile.
2025-09-11 Final fixes.
2025-09-18 Create can
2025-09-20 feat: Add ROS2 control and Gazebo dependencies to Dockerfile
    Added ROS2 control, controllers, control_msgs, joint-state-publisher-gui, xacro, gazebo-ros-pkgs, and gazebo-ros2-control to the devcontainer Dockerfile. Also cloned ros2_control_demos repository for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
2025-10-27 feat: Add mobile_robot ROS2 package with 4-wheel xacro model
    Introduces the mobile_robot package including CMakeLists.txt, package.xml, and a xacro model for a basic 4-wheel differential drive robot. Also adds comments in the devcontainer Dockerfile for catkin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
2025-10-27 feat: Add Gazebo simulation launch and robot model files
    Added Gazebo launch file and robot.gazebo for simulation support in mobile_robot. Updated robot.xacro with corrected wheel dimensions, joint positions, and included Gazebo plugin. Updated CMakeLists.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
2025-10-28 feat: vibe coded basic move back/forth rover
    Still need to add ROS2 control
2025-11-16 Added electrical folder
2025-11-21 Add some schematics
2025-12-08 Added some folders
2025-12-13 Added example for the REV BLDC
2025-12-13 Resolved merge conflicts
2025-12-13 Fix typo in HEARTBEAT_ID comment
2025-12-16 added new folders
2026-01-02 changed the folder title
2026-01-02 deleted folder
2026-01-02 change content of the folder
2026-01-12 upload pcb and schematics
2026-01-12 Fix image source in README for control board
2026-01-13 Add README content for High-Current Power Distribution Board
    Added detailed overview, features, and specifications for the High-Current Power Distribution Board.
2026-01-13 Clarify motor types in README.md
    Updated motor specifications for clarity.
2026-01-13 Revise PCB design considerations in README.md
    Updated PCB design considerations for high-current optimization, component layout, and power integrity analysis. Added figures for current density simulations before and after optimization.
2026-01-13 Fix image source paths in README.md
    Updated image source paths in README.md for clarity.
2026-01-13 Fix image source path in README.md
    Updated image source path for FEA after optimization.
2026-01-13 Fix image source paths in README.md
2026-01-13 Fix image tag formatting in README.md
    Updated image tag formatting for clarity.
2026-01-13 Fix image tag formatting in README.md
2026-01-13 Revise README with updated images and design objectives
    Updated image alt texts and added final board design section.
2026-01-13 Add final board design to README
    Added final board design section with image.
2026-01-13 Update README with final board design section
    Added final board design image to README.
2026-01-23 test
2026-01-23 Added new ROS2 folder for testing
2026-01-29 Update README with link to PCB details
2026-01-29 Update README with link to PCB schematics
2026-01-29 add new files
2026-03-14 Added Sparkcan library
2026-03-21 Added new folder
2026-05-13 Rover update
    1
2026-05-13 Change
    Change
2026-05-13 Add files via upload
    2024-2025 OakdLite angle orientation tracker
2026-05-13 feat: add IMU integration from Russell Code, add ZMQ subscriber
2026-05-13 feat: script that lists devices and available streams
2026-05-14 1
    1
2026-05-14 feat: integrate IMU data from teensy
2026-05-14 feat: fix stuff
2026-05-15 Summary
2026-05-15 Improve IMU fusion and ArUco blending
    Add angle wrapping helpers (wrap_pi, wrap_deg) and refine pose fusion between ArUco fixes, encoders and IMU. ArUco corrections are now gated by position/yaw error and by motion state with separate al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
2026-05-16 Add ArUco testing, calibration, and data
    Adds a set of ArUco marker test and calibration tools and accompanying data.
    Files added:
    - Rover/Tests/Aruco_distance_test.py: ArUco accuracy logger using RealSense to record pose samples to CSV for multiple distances/angles.
    - Rover/Tests/simple_test.py: Head-on distance sanity tests and CSV logging.
    - Rover/Tests/image_taker.py: Utility to capture calibration images from the RealSense camera.
    - Rover/Tests/calibration.py: Chessboard-based camera calibration script that saves camera intrinsics to an .npz file.
2026-05-16 Revise ArUco pose handling and payload
    Refactor perception pipeline to use camera-frame ArUco tvecs/yaw and remove interactive arena setup. Key changes:
    - Update MARKER_SIZE_METERS (0.20 -> 0.175) and add note that rear camera now sends raw tvecs + yaw; main rover code should perform arena transforms.
    - Remove interactive arena_choice prompt and hardcoded arena transforms; keep MARKER_GLOBAL_X/Z for compatibility.
    - Add calibrated rear camera_matrix and zero dist_coeffs used for pose estimates.
    - Introduce helper functions: wrap_to_pi, estimate_pose_single_marker (with estimatePoseSingleMarkers fallback to solvePnP), and rvec_to_yaw (preserves previous yaw correction convention).
    - Change A
2026-05-16 Add CAN rover control and telemetry tool
    Add Rover/Tools/new_can.ino: a new CAN-enabled control and telemetry tool for the autonomous rover. Integrates Sabertooth serial motor commands, FlexCAN receive/send handlers, encoder-based distance 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
2026-05-16 Add mainrs.txt for ArUco and IMU localization
